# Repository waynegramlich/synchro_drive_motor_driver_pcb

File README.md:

# synchro_drive_motor_driver_pcb

This printed circuit board drives two brushed DC motors for a
synchro drive.   A synchro drive allows a single wheel to
be driven and turned independently without any wheel skidding.

## Revision A

This board is designed around U1 and U2, a couple of AS5050
hall effect 10-bit absolute rotation sensors.  The board is
arrange to place both of these sensors exactly over the
magnets on top of the twist motor and drive motor shafts.

The board geometry is constrained by synchro drive motor
assembly.  The motor pulleys are fully enclosed to keep
dirt and grime from gumming up the pulleys.  Thus, the
PCB has an enclosed section on the bottom and an
exposed section on the top.  The exposed section is where
all of the heat generating electronics is placed to provide
additional air flow to remove excess heat.

The electronics is divided into two electrically isolated
sections:

* The processor section is connected to the Logic power/ground
  and can communicate over the CAN bus.

* The motor section is connected to the Motor power/ground
  and drives the motor H-bridges.

### Processor Section

The power and communication comes in on the 26-pin N1 connector.

The motor power (MPWR) and motor ground (MGND) are routed to
the motor section (see below.)

The logic power (LPWR) and logic ground (LGND) are sent through
C1, U3, C3, U6, C9, and C11 to provide regulated 5 volts and 3.3
volts.  The LM2931 (U3) is must be able to take up to 30 volts
input.  This requires a DPAK package to provide adequate heat
dissipation.  C3 must be a tantalum capacitor to get an ESR
(Equivalent Series Resistance) less than 400mOhm.

There are two signals (SEL_LR and SEL_FB) that can be
testing in software to specify whether the wheel is left/right
or front/back.

The communication comes in over CANH and CANL and is run into
an MCP2562 (U4) CAN bus transceiver.  The MCP2562 is the only
part that must run at 5 volts.  By setting the VIO input (pin 5)
to 3.3V the processor can directly communicate with the transceiver
using 3.3V signaling.

The processor is TM4C123GH6PM, an Arm Cortex M4-F class
microcontroller.  The processor is run using a 10MHz crystal
X1 and two 18pF capactiors C10 and C11.  There is a reset
button (SW1) with a 10K pull-up resistor (R2).

The AS5050 hall effect rotation sensors (U1 and U2) are each
tied to a dedicated SPI intefaces (SSI0 and SSI1, repsectively.)

For debugging, there is 6-pin connector (N2) that is designed
to connect to FTDI 3.3V USB to serial cable.  The LED (D1) and
current limiting resistor (R1) are also available for debugging.
Jumper J1 is meant to implement physical signal that allows\
over the bus firmware updating to be enabled or disabled.  J1
is also available for debugging.

The processor can be programmed and debugged via either of the
JTAG/SWDEBUG connectors (N3 or N4).  Both connectors conform to
the ARM 10-pin JTAG/SWDEBUG connector specification.  One connector
is .05inch pitch and the other is .10inch pitch.

The motor directions are specified by PB0-3 (pins 45-48).
Third SPI peripheral (SSI3) is dedicated to controlling the DAC
(Digital to Analog Converter) in the motor section.

There are the usual bypass capacitors (C2-C8, C22-23)
and mounting holes (H1-H4, H6-H9).  There are two additional
holes (H5, H10) that are aligned with the motor drive shafts.

### Motor section

Motor power is passed through C13, U7, and U14 to provide
regulated 5V for the various integrated circuits.  There is
no 3.3V in this section.

The H-bridges are venerable bipolar L298's (U13, U14) with
8 Schottky current shunt diodes.  The L298's are dual H-bridges
that have been ganged together to provide 3A of continuous
current.  The motors are connected to N5 and N6.

The direction control signals change infrequently, so they
are directed through inexpensive (and lower bandwidth)
optoisolator chips (U10, U11) with current limit resistors
(R3-R6).  Resistors R7-R10 are pull-up resistors that are
fed into IN1-IN4 inputs of the H-bridge chips.

The DAC is controlled with SPI signaling through the SI8420
chips.  This are electrically isolated chips that can send
digital signals at up to 1MHz.  The SEL, SCK and SDI signals
are sent through these chip to the DAC chip (U15).

The DAC chip is an MCP48?2, which a dual channel DAC.
The output of each DAC is used to set the maximum voltage
across the H-bridge current sense resistors (R11, R12).
The DAC outputs are compared to the sense resistor voltages
using the MCP6542 comparator chip (U16).  Whenever the
current through the sense resistor exceeds the DAC output
voltage, the enable pins for the L298 are cleared through
the dual D flip-flops (U12).

The way this works, is that the processor sends out a
25KHz square wave through U9 (pin 2).  This signal clocks
a 1 into both flip-flops, thereby enabling both H-bridges.
As the current builds up across the current sense resistor,
the flip-flops are cleared to disable the H-bridge enable
pin.  This results in a PWM (pulse width modulated) signal
on the H-bridge enable pin, where the electronics ensures
that the maximum amount of current specified by the DAC
voltage is not exceeded.

There are the usual set of bypass capacitors (C15-C21)
and test points for debugging.

### Rev. A Notes

* The current sense resistor is too big.  At maximum
  current (3A), the resistor will generate 5W of power.
  The current sense resistors are only 2W devices.
  The resistor needs to be dropped from .56 Ohm to
  .2 Ohm.  This will require changing the DAC to
  be one that has a maximum voltage input rather
  than an internally generated one.

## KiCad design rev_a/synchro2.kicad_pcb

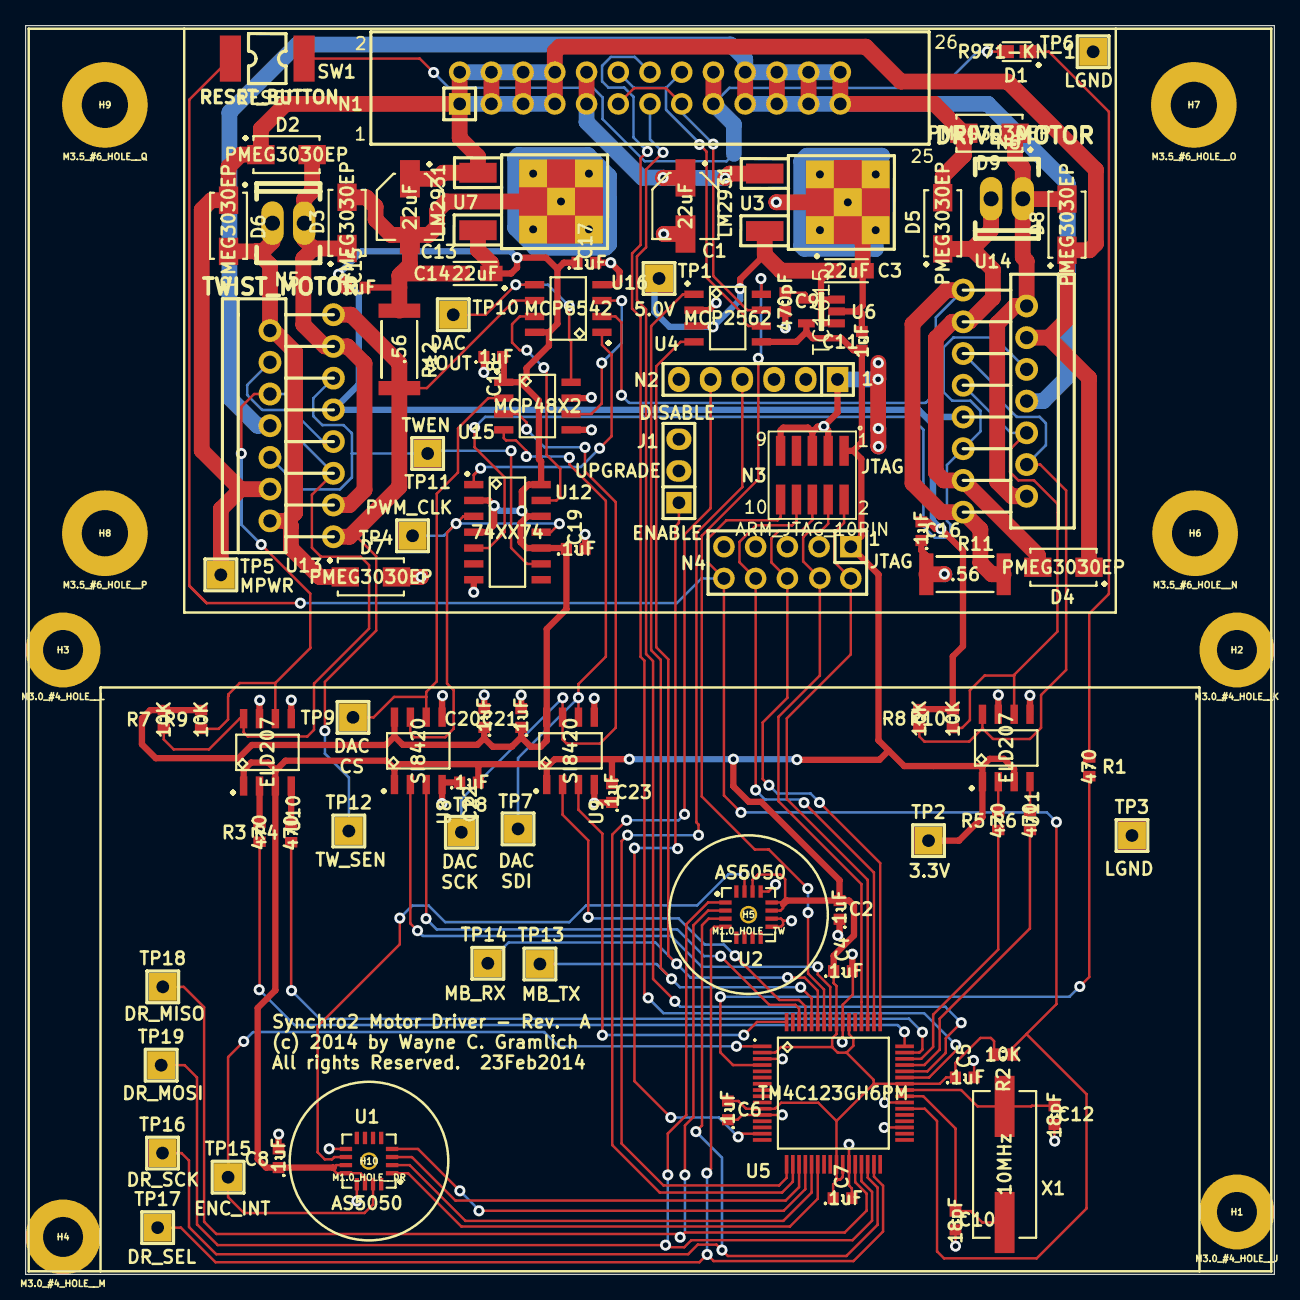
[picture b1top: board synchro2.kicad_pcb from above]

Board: 2 copper layers, 100.0 x 100.0 mm, 98 parts (0 on the bottom side), 69 nets.

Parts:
C1, C13: 22uF; CAPAE530X540N
C2, C4, C5, C6, C7, C8, C15, C16, C17, C18, C19, C20, C21, C22, C23: .1uF; CAPC1608X55N
C3, C14: 22uF; CAPMP3216X180N
C9: 470pF; CAPC1608X55N
C10, C12: 18pF; CAPC1608X55N
C11: 1uF; CAPC1608X55N
D1: R971-KN-1; DIOM2012X160N
D2, D3, D4, D5, D6, D7, D8, D9: PMEG3030EP; DIOM5027X244N
H1: M3.0_#4_HOLE__J; M3.0_#4_HOLE
H2: M3.0_#4_HOLE__K; M3.0_#4_HOLE
H3: M3.0_#4_HOLE__L; M3.0_#4_HOLE
H4: M3.0_#4_HOLE__M; M3.0_#4_HOLE
H5: M1.0_HOLE__TW; M1.0_HOLE
H6: M3.5_#6_HOLE__N; M3.5_#6_HOLE
H7: M3.5_#6_HOLE__O; M3.5_#6_HOLE
H8: M3.5_#6_HOLE__P; M3.5_#6_HOLE
H9: M3.5_#6_HOLE__Q; M3.5_#6_HOLE
H10: M1.0_HOLE__DR; M1.0_HOLE
J1: UPDATE_ENABLE; Pin_Header_Straight_1x03
N1: OMRON XG4A-2632; OMRON_X4GA_2632
N2: FTDI_CONN; Pin_Header_Straight_1x06
N3: ARM_JTAG_10PIN; SMT_VERT_M1.27_2x5
N4: ARM_JTAG_10PIN; ARM_JTAG_2X5_2.54MM
N5: TWIST_MOTOR; Socket_MOLEX-KK-RM2-54mm_Lock_2pin_straight
N6: DRIVE_MOTOR; Socket_MOLEX-KK-RM2-54mm_Lock_2pin_straight
R1, R3, R4, R5, R6: 470; RESC1608X50N
R2, R7, R8, R9, R10: 10K; RESC1608X50N
R11, R12: .56; RESC6432X76N
SW1: RESET_BUTTON; KSS221GLFS
TP1: L5.0V; TEST_POINT
TP2: L3.3V; TEST_POINT
TP3: LGND; TEST_POINT
TP4: PWM_CLK; TEST_POINT
TP5: MPWR; TEST_POINT
TP6: MGND; TEST_POINT
TP7: DAC_SDI; TEST_POINT
TP8: DAC_SCK; TEST_POINT
TP9: DAC_CS; TEST_POINT
TP10: DAC_AOUT; TEST_POINT
TP11: TWEN; TEST_POINT
TP12: TW_SEN; TEST_POINT
TP13: MB_TX; TEST_POINT
TP14: MB_RX; TEST_POINT
TP15: ENC_INT; TEST_POINT
TP16: DR_SCLK; TEST_POINT
TP17: DR_SEL; TEST_POINT
TP18: DR_MISO; TEST_POINT
TP19: DR_MOSI; TEST_POINT
U1, U2: AS5050; QFN65P400X400X80-16N
U3, U7: LM2931; DPAK_THERMAL
U4: MCP2562; SOIC127P600X175-8N
U5: TM4C123GH6PM; QFP50P1200X1200X145-64N
U6: TC1015; SOT95P280X145-5N
U8, U9: SI8420; SOIC127P600X175-8N
U10, U11: ELD207; SOIC127P600X175-8N
U12: 74XX74; SOIC127P600X175-14N
U13, U14: L298; MULTIWATT15
U15: MCP48X2; SOIC127P600X175-8N
U16: MCP6542; SOIC127P600X175-8N
X1: 10MHz; XTAL1150X480X430N

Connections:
3.3V: C2.1, C4.1, C5.1, C6.1, C7.1, C8.1, C11.1, C22.1, C23.1, N3.1, N4.1, R2.2, TP2.1, U1.11, U1.12, U1.14, U2.11, U2.12, U2.14, U4.5, U5.2, U5.11, U5.25, U5.26, U5.42, U5.54, U5.56, U6.5, U8.1, U9.1, U10.1, U10.3, U11.1, U11.3
/5V: C3.1, TP1.1, U3.3, U4.3, U6.1, U6.3
/DR_MISO: TP18.1, U2.2, U5.28
/DR_MOSI: TP19.1, U2.1, U5.29
/DR_SCLK: TP16.1, U2.3, U5.30
/LPWR: C1.1, N1.9, N1.10, U3.1
/MB_RX: TP14.1, U4.4, U5.59
/MB_TX: TP13.1, U4.1, U5.60
/Motor_Power/DR+: D8.2, D9.1, N6.1, U14.2, U14.14
/Motor_Power/DR-: D4.2, D5.1, N6.2, U14.3, U14.13
/Motor_Power/DRD1: R8.1, U11.8, U14.5, U14.12
/Motor_Power/DRD2: R10.1, U11.6, U14.7, U14.10
/Motor_Power/DREN: U12.5, U14.6, U14.11
/Motor_Power/DR_SEN: R11.2, U14.1, U14.15, U16.2
/Motor_Power/M5V: C14.1, C15.1, C16.1, C17.1, C18.1, C19.1, C20.1, C21.1, R7.2, R8.2, R9.2, R10.2, U7.3, U8.8, U9.8, U12.2, U12.4, U12.10, U12.12, U12.14, U13.9, U14.9, U15.1, U16.8
/Motor_Power/MB_DAC_CLK: U5.61, U9.2
/Motor_Power/MB_DR_EN1: R5.1, U5.46
/Motor_Power/MB_DR_EN2: R6.1, U5.45
/Motor_Power/MB_MGND: C13.2, C14.2, C15.2, C16.2, C17.2, C18.2, C19.2, C20.2, C21.2, D3.2, D5.2, D7.2, D9.2, N1.19, N1.20, N1.21, N1.22, N1.23, N1.24, N1.25, N1.26, R11.1, R12.1, TP6.1, U7.2, U8.5, U9.5, U10.5, U10.7, U11.5, U11.7, U12.7, U13.8, U14.8, U15.5, U15.7, U16.4
/Motor_Power/MB_MOSI: U5.64, U9.3
/Motor_Power/MB_MPWR: C13.1, D2.1, D4.1, D6.1, D8.1, N1.1, N1.2, N1.3, N1.4, N1.5, N1.6, N1.7, N1.8, TP5.1, U7.1, U13.4, U14.4
/Motor_Power/MB_PWM_CLK: U5.57, U8.2
/Motor_Power/MB_TW_EN1: R3.1, U5.48
/Motor_Power/MB_TW_EN2: R4.1, U5.47
/Motor_Power/TW+: D6.2, D7.1, N5.1, U13.2, U13.14
/Motor_Power/TW-: D2.2, D3.1, N5.2, U13.3, U13.13
/Motor_Power/TWD1: R7.1, U10.8, U13.5, U13.12
/Motor_Power/TWD2: R9.1, U10.6, U13.7, U13.10
/Motor_Power/TWEN: TP11.1, U12.9, U13.6, U13.11
/Motor_Power/TW_SEN: R12.2, TP12.1, U13.1, U13.15, U16.6
/Motor_Power/~MB_DAC_SEL: U5.62, U8.3
/SEL_FB: N1.14, U5.43
/SEL_LR: N1.13, U5.44
/TCK: N3.4, N4.4, U5.52
/TDI: N3.8, N4.8, U5.50
/TDO: N3.6, N4.6, U5.49
/TMS: N3.2, N4.2, U5.51
/TW_MISO: U1.2, U5.21
/TW_MOSI: U1.1, U5.22
/TW_SCK: U1.3, U5.19
/UART_RX: N2.4, U5.17
/UART_TX: N2.5, U5.18
/~DR_SEL: TP17.1, U2.4, U5.31
/~RESET: N3.10, N4.10, R2.1, SW1.1, U5.38
/~TW_SEL: U1.4, U5.20
GND: C1.2, C2.2, C3.2, C4.2, C5.2, C6.2, C7.2, C8.2, C9.2, C10.2, C11.2, C12.2, C22.2, C23.2, D1.2, J1.2, N1.17, N1.18, N2.1, N3.3, N3.5, N3.9, N4.3, N4.5, N4.9, SW1.2, TP3.1, U1.9, U1.13, U2.9, U2.10, U2.13, U3.2, U4.2, U5.3, U5.12, U5.27, U5.35, U5.39, U5.55, U6.2, U8.4, U9.4
unnamed: C9.1, U6.4
unnamed: C10.1, U5.40, X1.1
unnamed: C12.1, U5.41, X1.2
unnamed: D1.1, R1.1
unnamed: J1.1, U5.15
unnamed: N1.11, N1.15, U4.7
unnamed: N1.12, N1.16, U4.6
unnamed: R1.2, U5.4
unnamed: R3.2, U10.2
unnamed: R4.2, U10.4
unnamed: R5.2, U11.2
unnamed: R6.2, U11.4
unnamed: TP4.1, U8.7, U12.3, U12.11
unnamed: TP7.1, U9.6, U15.4
unnamed: TP8.1, U9.7, U15.3
unnamed: TP9.1, U8.6, U15.2
unnamed: TP10.1, U15.8, U16.5
unnamed: TP15.1, U1.15, U5.1
unnamed: U1.10, U2.15
unnamed: U4.8, U5.58
unnamed: U12.1, U16.1
unnamed: U12.13, U16.7
unnamed: U15.6, U16.3

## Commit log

2014-02-01 Basic schematic is done.
2014-02-25 Rev. A is pretty close to being ready.
2014-02-25 Almost done with Rev. A.
2014-02-26 Rev. A is ready.
2014-03-03 Tweak compennt values to match pricing database. No footprints were changed.

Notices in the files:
rev_a/synchro2.kicad_pcb:
(c) 2014 by Wayne C. Gramlich
All rights Reserved.  23Feb2014
